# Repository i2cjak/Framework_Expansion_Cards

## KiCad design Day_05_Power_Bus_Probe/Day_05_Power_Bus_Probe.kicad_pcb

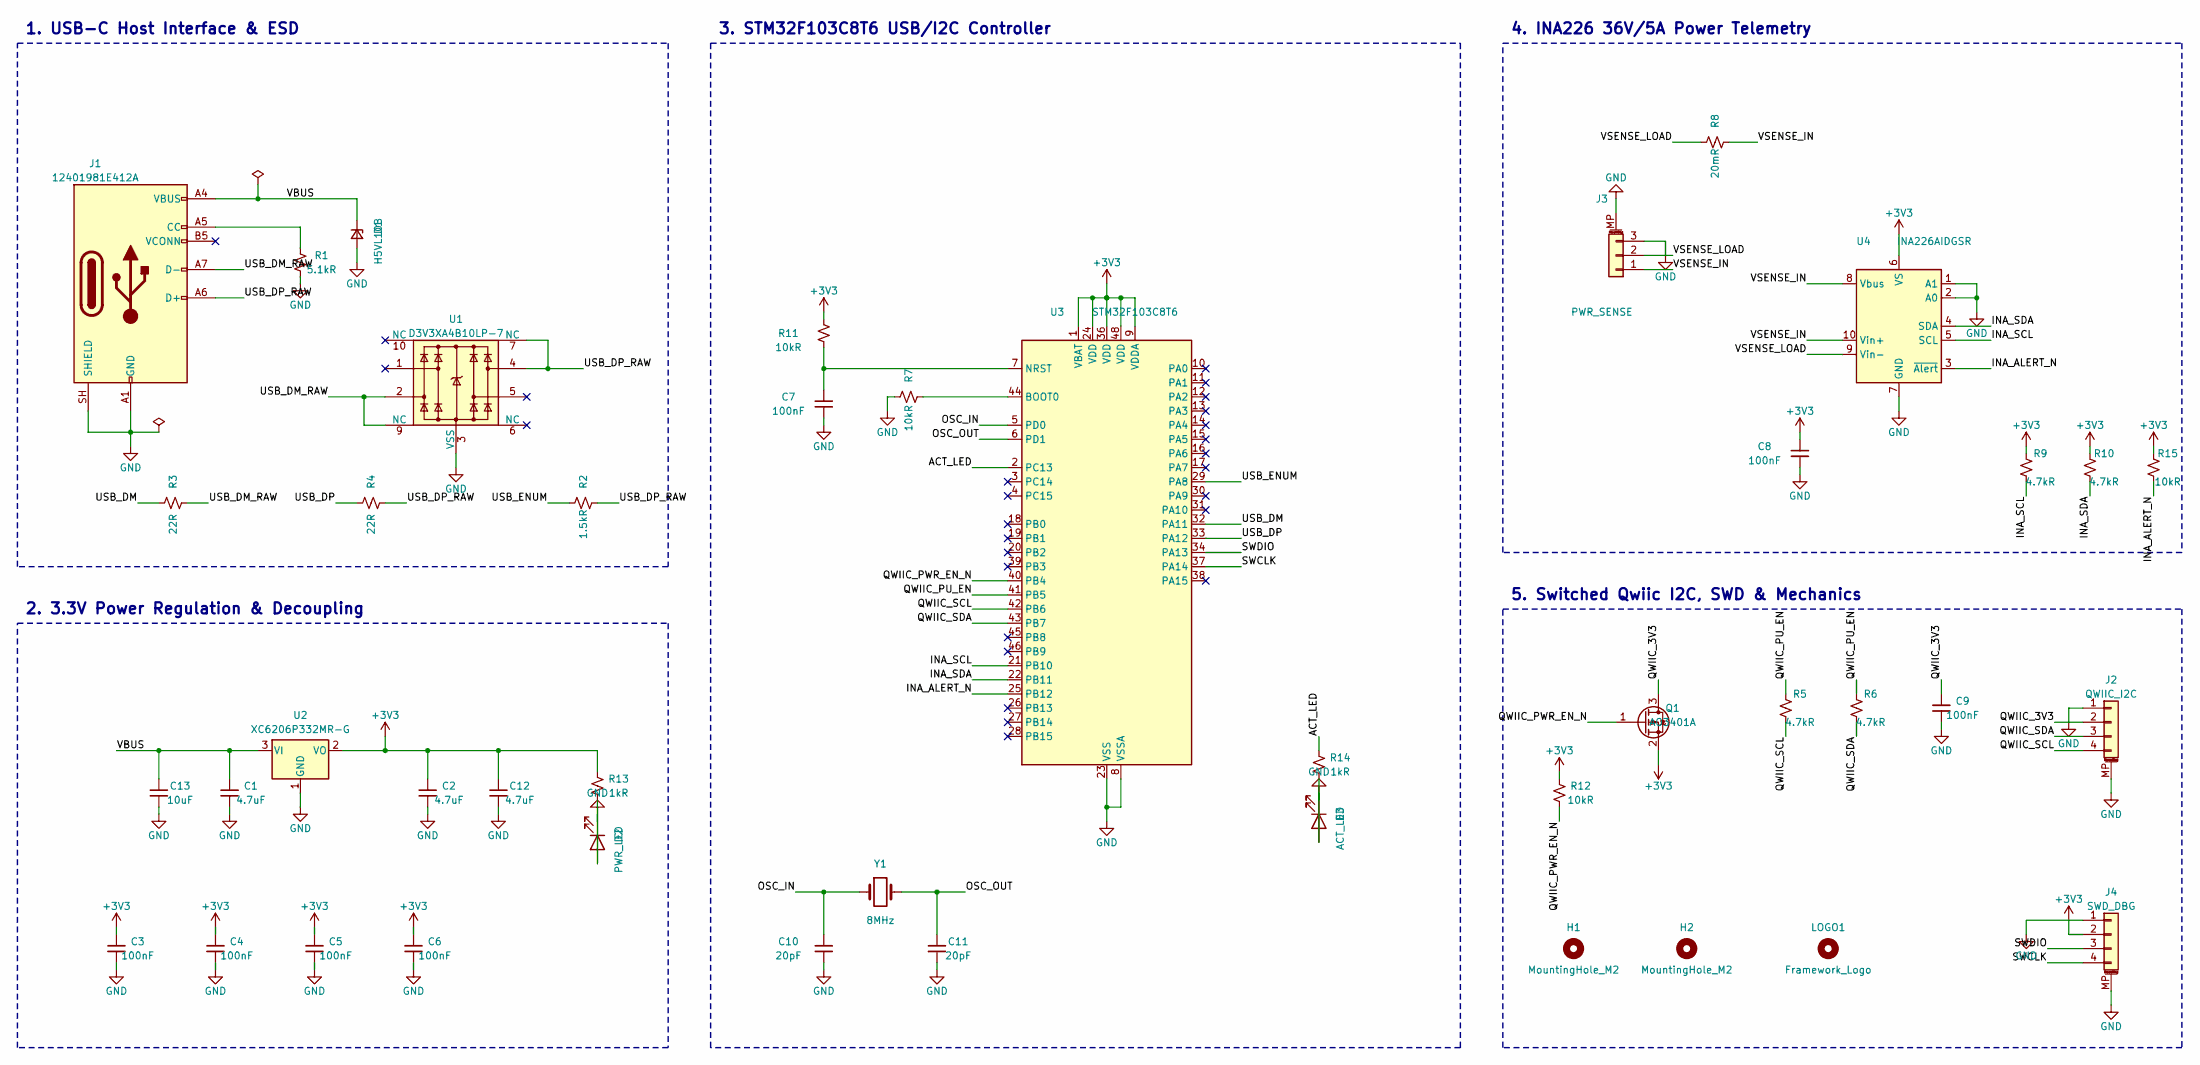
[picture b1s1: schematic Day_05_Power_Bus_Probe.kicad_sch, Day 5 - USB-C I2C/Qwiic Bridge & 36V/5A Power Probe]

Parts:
C1, C2, C12: 4.7uF; C_0603_1608Metric; MPN CL10A475KO8NNNC; LCSC C19666
C3, C4, C5, C6, C7, C8, C9: 100nF; C_0402_1005Metric; MPN CL05B104KB54PNC; LCSC C307331
C10, C11: 20pF; C_0402_1005Metric; MPN 0402CG200J500NT; LCSC C1554
C13: 10uF; C_0805_2012Metric; MPN CL21A106KAYNNNE; LCSC C15850
D1: H5VL10B; D_SOD-882; MPN H5VL10B; LCSC C7420372
D2: PWR_LED; LED_0603_1608Metric; MPN KT-0603W; LCSC C2290
D3: ACT_LED; LED_0603_1608Metric; MPN KT-0603R; LCSC C2286
H1, H2: MountingHole_M2; MountingHole_2.2mm_M2
J1: 12401981E412A; USB_C_Plug_Amphenol_12401981E412A; MPN 12401981E412A; LCSC C5428559
J2: QWIIC_I2C; JST_SH_SM04B-SRSS-TB_1x04-1MP_P1.00mm_Horizontal; MPN SM04B-SRSS-TB(LF)(SN); LCSC C160404
J3: PWR_SENSE; JST_PH_S3B-PH-SM4-TB_1x03-1MP_P2.00mm_Horizontal; MPN S3B-PH-SM4-TB(LF)(SN); LCSC C265101
J4: SWD_DBG; JST_SH_SM04B-SRSS-TB_1x04-1MP_P1.00mm_Horizontal; MPN SM04B-SRSS-TB(LF)(SN); LCSC C160404
LOGO1: Framework_Logo; Framework-Logo_1.5mm_SilkScreen
Q1: AO3401A; SOT-23; MPN AO3401A; LCSC C15127
R1: 5.1kR; R_0402_1005Metric; MPN 0402WGF5101TCE; LCSC C25905
R2: 1.5kR; R_0402_1005Metric; MPN 0402WGF1501TCE; LCSC C25867
R3, R4: 22R; R_0402_1005Metric; MPN 0402WGF220JTCE; LCSC C25092
R5, R6, R9, R10: 4.7kR; R_0402_1005Metric; MPN 0402WGF4701TCE; LCSC C25900
R7, R11, R12, R15: 10kR; R_0402_1005Metric; MPN 0402WGF1002TCE; LCSC C25744
R8: 20mR; R_1206_3216Metric; MPN 1206W3F200MT5E; LCSC C2765435
R13, R14: 1kR; R_0402_1005Metric; MPN 0402WGF1001TCE; LCSC C11702
U1: D3V3XA4B10LP-7; Diodes_UDFN-10_1x2.5mm_P0.5mm; MPN D3V3XA4B10LP-7; LCSC C1980462
U2: XC6206P332MR-G; SOT-23; MPN XC6206P332MR-G; LCSC C5446
U3: STM32F103C8T6; LQFP-48_7x7mm_P0.5mm; MPN STM32F103C8T6; LCSC C8734
U4: INA226AIDGSR; MSOP-10_3x3mm_P0.5mm; MPN INA226AIDGSR; LCSC C49851
Y1: 8MHz; Crystal_SMD_5032-2Pin_5.0x3.2mm; MPN X50328MSB2GI; LCSC C115962

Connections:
/ACT_LED: R14.1, U3.2 (PC13)
/INA_ALERT_N: R15.2, U3.25 (PB12), U4.3 (~Alert)
/INA_SCL: R9.2, U3.21 (PB10), U4.5 (SCL)
/INA_SDA: R10.2, U3.22 (PB11), U4.4 (SDA)
/OSC_IN: C10.1, U3.5 (PD0), Y1.1
/OSC_OUT: C11.1, U3.6 (PD1), Y1.2
/QWIIC_PU_EN: R5.1, R6.1, U3.41 (PB5)
/QWIIC_PWR_EN_N: Q1.1 (G), R12.2, U3.40 (PB4)
/QWIIC_SCL: J2.4, R5.2, U3.42 (PB6)
/QWIIC_SDA: J2.3, R6.2, U3.43 (PB7)
/SWCLK: J4.4, U3.37 (PA14)
/SWDIO: J4.3, U3.34 (PA13)
/USB_DM: R3.1, U3.32 (PA11)
/USB_DM_RAW: J1.A7 (D-), R3.2, U1.2, U1.9 (NC)
/USB_DP: R4.1, U3.33 (PA12)
/USB_DP_RAW: J1.A6 (D+), R2.2, R4.2, U1.4, U1.7 (NC)
/USB_ENUM: R2.1, U3.29 (PA8)
/VBUS: C1.1, C13.1, D1.1 (K), J1.A4 (VBUS), J1.A9 (VBUS), J1.B4 (VBUS), J1.B9 (VBUS), U2.3 (VI)
/VSENSE_IN: J3.1, R8.2, U4.8 (Vbus), U4.10 (Vin+)
unnamed: J1.A5 (CC), R1.1
unnamed: R7.2, U3.44 (BOOT0)
unnamed: C7.1, R11.2, U3.7 (NRST)

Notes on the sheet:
1. USB-C Host Interface & ESD
2. 3.3V Power Regulation & Decoupling
3. STM32F103C8T6 USB/I2C Controller
4. INA226 36V/5A Power Telemetry
5. Switched Qwiic I2C, SWD & Mechanics

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
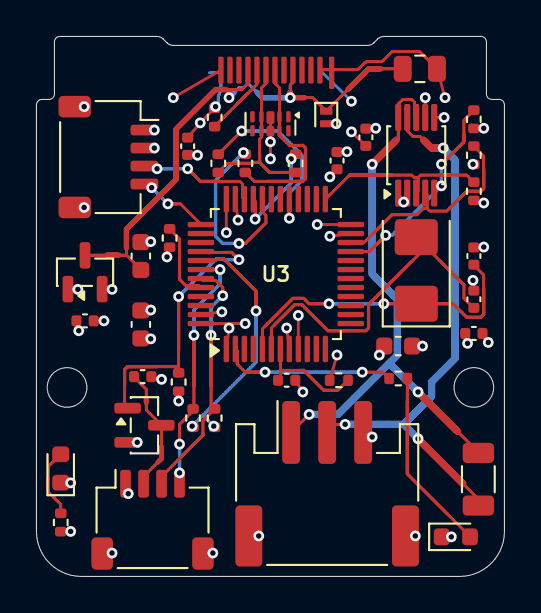
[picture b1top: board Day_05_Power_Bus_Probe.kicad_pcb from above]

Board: 4 copper layers, 26.0 x 30.0 mm, 44 parts (1 on the bottom side), 28 nets.
